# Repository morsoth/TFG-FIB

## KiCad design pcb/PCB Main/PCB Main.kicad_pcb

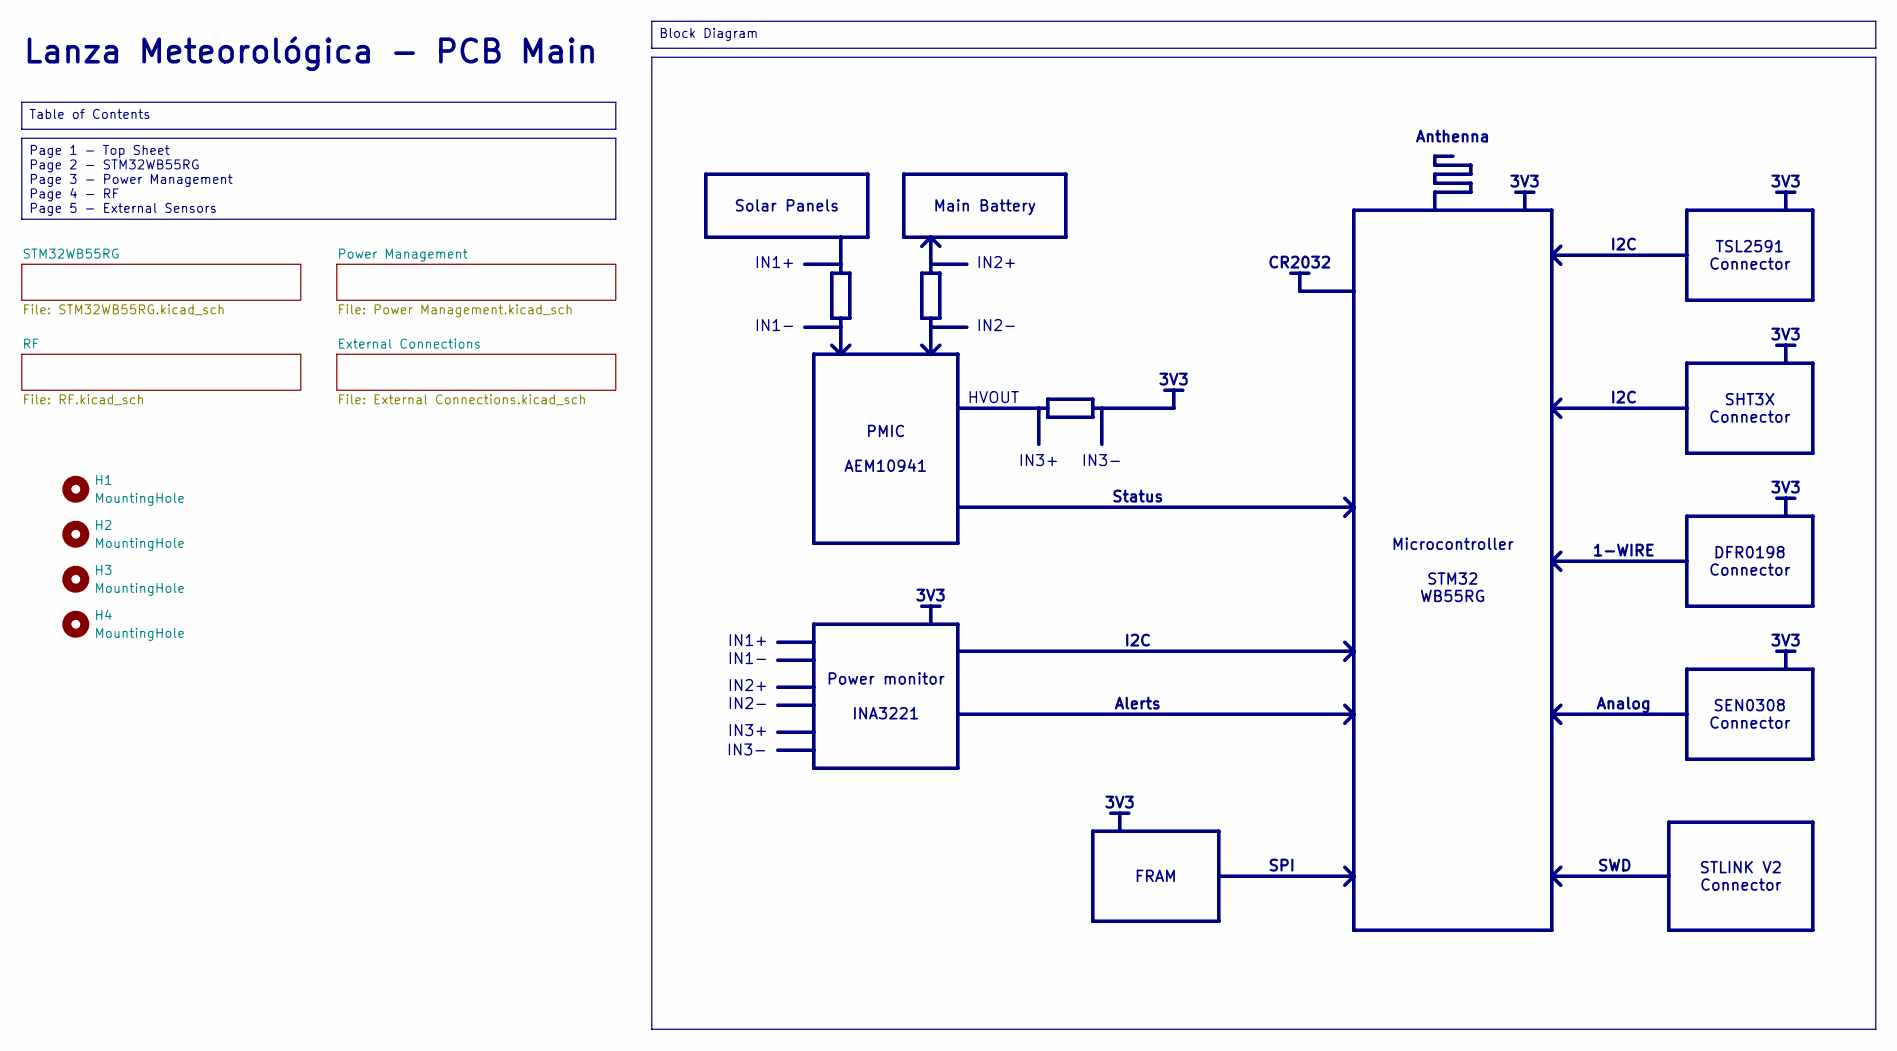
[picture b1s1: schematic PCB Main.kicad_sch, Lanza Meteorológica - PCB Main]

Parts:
H1, H2, H3, H4: MountingHole; MountingHole_2.2mm_M2

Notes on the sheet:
3V3
IN3+
IN2-
SPI
IN1-
Analog
I2C
Anthenna
IN1+
IN3-
Status
Lanza Meteorológica - PCB Main
HVOUT
SWD
IN2+
1-WIRE
Alerts
CR2032
PMIC AEM10941
Page 1 - Top Sheet Page 2 - STM32WB55RG Page 3 - Power Management Page 4 - RF Page 5 - External Sensors
SHT3X Connector
Solar Panels
STLINK V2 Connector
Table of Contents
FRAM
Main Battery
Block Diagram
DFR0198 Connector
Microcontroller STM32 WB55RG
SEN0308 Connector
TSL2591 Connector
Power monitor INA3221

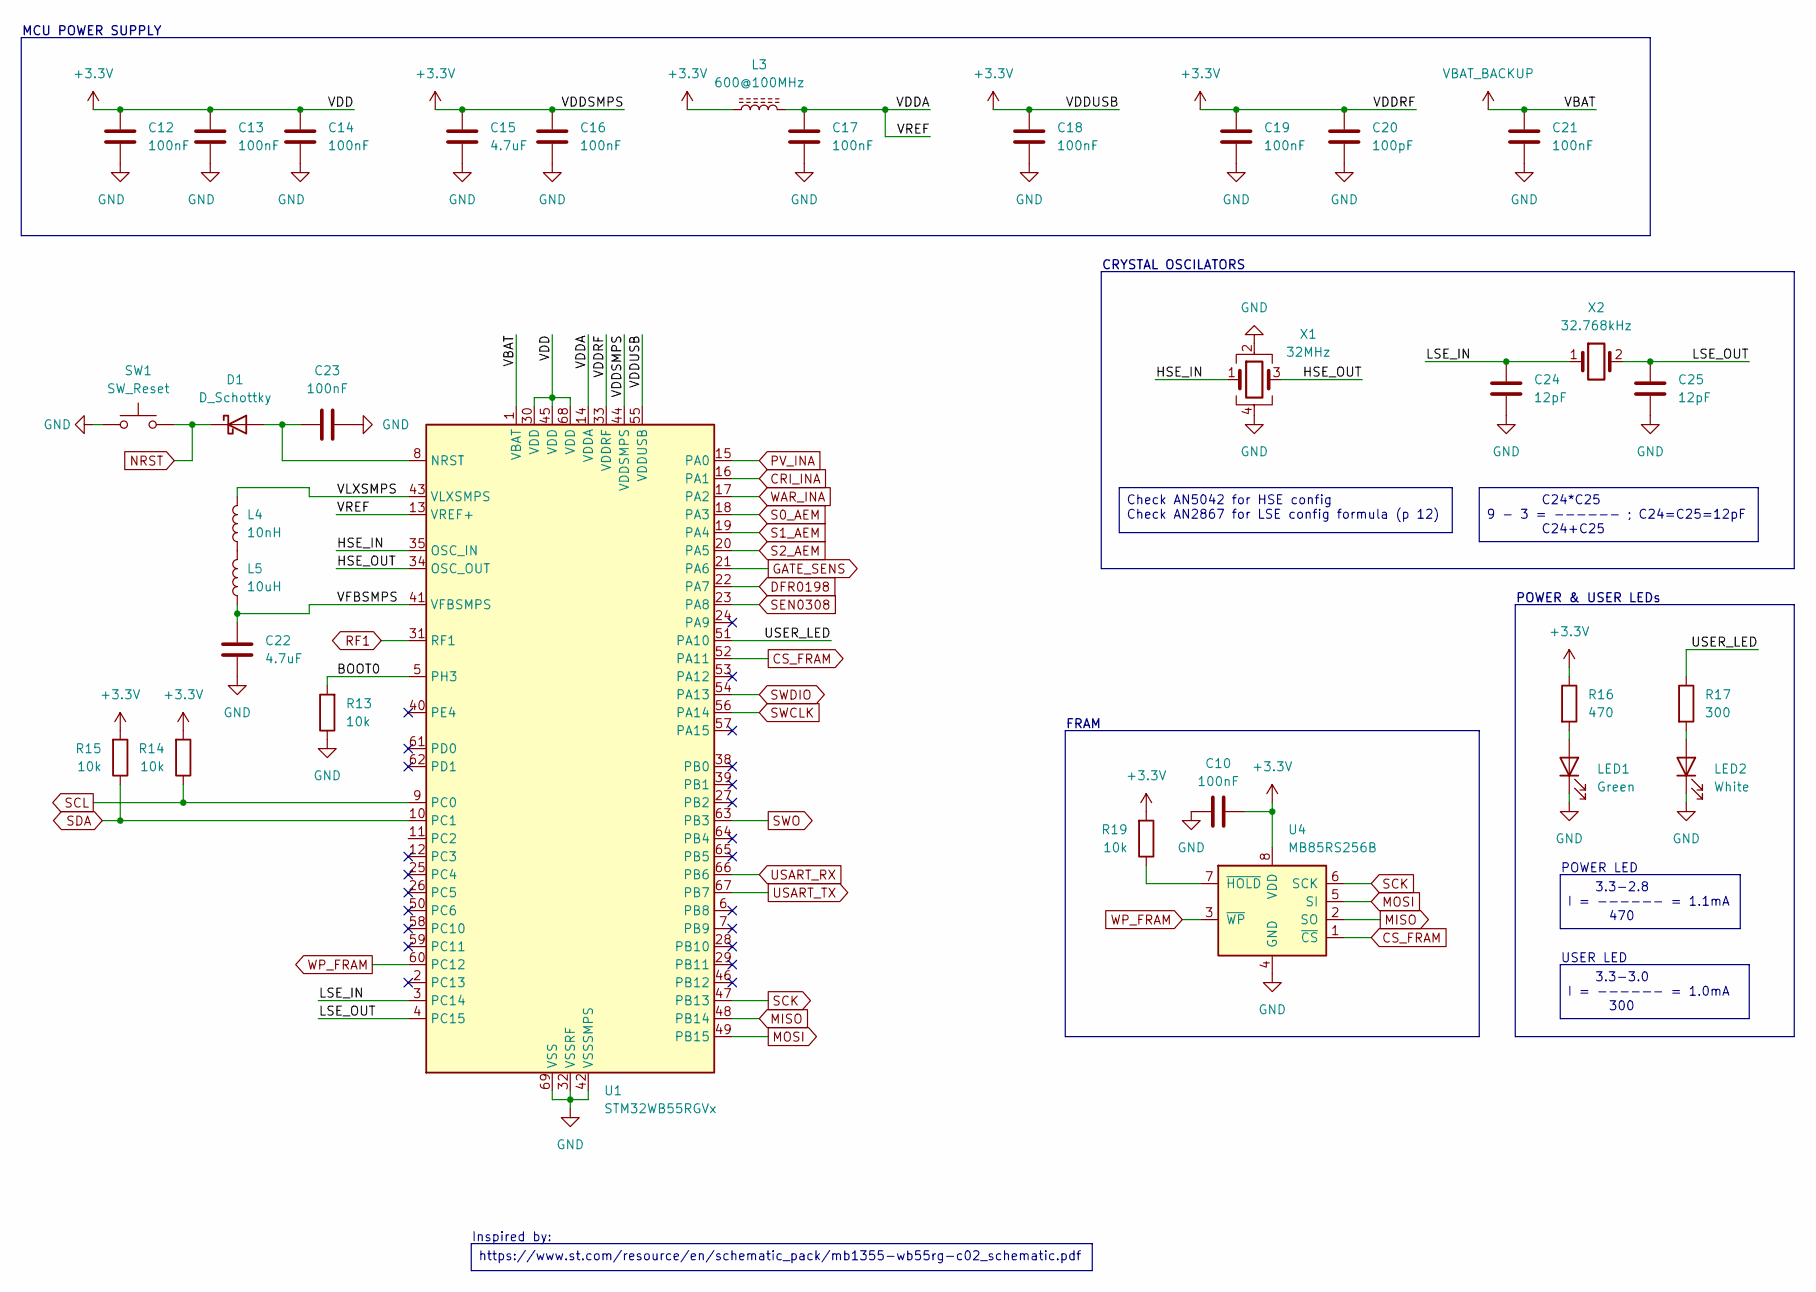
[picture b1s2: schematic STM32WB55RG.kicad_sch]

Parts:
C10, C12, C13, C14, C16, C17, C18, C19, C21, C23: 100nF; C_0402_1005Metric
C15, C22: 4.7uF; C_0402_1005Metric
C20: 100pF; C_0402_1005Metric
C24, C25: 12pF; C_0402_1005Metric
D1: D_Schottky; D_SOD-323
L3: 600@100MHz; L_0603_1608Metric
L4: 10nH; L_0402_1005Metric
L5: 10uH; L_0805_2012Metric
LED1: Green; LED_0805_2012Metric
LED2: White; LED_0805_2012Metric
R13, R14, R15, R19: 10k; R_0402_1005Metric
R16: 470; R_0603_1608Metric
R17: 300; R_0603_1608Metric
SW1: SW_Reset; SW_SPST_TL3342
U1: STM32WB55RGVx; QFN-68-1EP_8x8mm_P0.4mm_EP6.4x6.4mm
U4: MB85RS256B; SOIC-8_3.9x4.9mm_P1.27mm
X1: 32MHz; Crystal_SMD_2016-4Pin_2.0x1.6mm
X2: 32.768kHz; Crystal_SMD_2012-2Pin_2.0x1.2mm

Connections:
+3.3V: C10.1, C12.2, C13.2, C14.2, C15.2, C16.2, C18.2, C19.2, C20.2, L3.1, R14.2, R15.2, R16.1, R19.2, U1.30 (VDD), U1.33 (VDDRF), U1.44 (VDDSMPS), U1.45 (VDD), U1.55 (VDDUSB), U1.68 (VDD), U4.8 (VDD); also elsewhere on the board
/STM32WB55RG/BOOT0: R13.2, U1.5 (PH3)
/STM32WB55RG/HSE_IN: U1.35 (OSC_IN), X1.1
/STM32WB55RG/HSE_OUT: U1.34 (OSC_OUT), X1.3
/STM32WB55RG/LSE_IN: C24.2, U1.3 (PC14), X2.1
/STM32WB55RG/LSE_OUT: C25.2, U1.4 (PC15), X2.2
/STM32WB55RG/USER_LED: R17.1, U1.51 (PA10)
/STM32WB55RG/VDDA: C17.2, L3.2, U1.13 (VREF+), U1.14 (VDDA)
/STM32WB55RG/VFBSMPS: C22.2, L5.1, U1.41 (VFBSMPS)
/STM32WB55RG/VLXSMPS: L4.2, U1.43 (VLXSMPS)
CRI_INA: U1.16 (PA1); also elsewhere on the board
CS_FRAM: U1.52 (PA11), U4.1 (~CS)
DFR0198: U1.22 (PA7); also elsewhere on the board
GATE_SENS: U1.21 (PA6); also elsewhere on the board
GND: C10.2, C12.1, C13.1, C14.1, C15.1, C16.1, C17.1, C18.1, C19.1, C20.1, C21.1, C22.1, C23.1, C24.1, C25.1, LED1.1 (K), LED2.1 (K), R13.1, SW1.1, U1.32 (VSSRF), U1.42 (VSSSMPS), U1.69 (VSS), U4.4 (GND), X1.2, X1.4; also elsewhere on the board
MISO: U1.48 (PB14), U4.2 (SO)
MOSI: U1.49 (PB15), U4.5 (SI)
NRST: D1.1 (K), SW1.2; also elsewhere on the board
unnamed: C23.2, D1.2 (A), U1.8 (NRST)
unnamed: L4.1, L5.2
unnamed: LED1.2 (A), R16.2
unnamed: LED2.2 (A), R17.2
unnamed: R19.1, U4.7 (~HOLD)
PV_INA: U1.15 (PA0); also elsewhere on the board
RF1: U1.31 (RF1); also elsewhere on the board
S0_AEM: U1.18 (PA3); also elsewhere on the board
S1_AEM: U1.19 (PA4); also elsewhere on the board
S2_AEM: U1.20 (PA5); also elsewhere on the board
SCK: U1.47 (PB13), U4.6 (SCK)
SCL: R14.1, U1.9 (PC0); also elsewhere on the board
SDA: R15.1, U1.10 (PC1); also elsewhere on the board
SEN0308: U1.23 (PA8); also elsewhere on the board
SWCLK: U1.56 (PA14); also elsewhere on the board
SWDIO: U1.54 (PA13); also elsewhere on the board
SWO: U1.63 (PB3); also elsewhere on the board
USART_RX: U1.66 (PB6); also elsewhere on the board
USART_TX: U1.67 (PB7); also elsewhere on the board
VBAT_BACKUP: C21.2, U1.1 (VBAT); also elsewhere on the board
WAR_INA: U1.17 (PA2); also elsewhere on the board
WP_FRAM: U1.60 (PC12), U4.3 (~WP)

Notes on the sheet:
Inspired by:
CRYSTAL OSCILATORS
POWER & USER LEDs
FRAM
POWER LED
USER LED
MCU POWER SUPPLY
3.3-2.8 I = ------ = 1.1mA 470
https://www.st.com/resource/en/schematic_pack/mb1355-wb55rg-c02_schematic.pdf
Check AN5042 for HSE config Check AN2867 for LSE config formula (p 12)
3.3-3.0 I = ------ = 1.0mA 300
C24*C25 9 - 3 = ------ ; C24=C25=12pF C24+C25

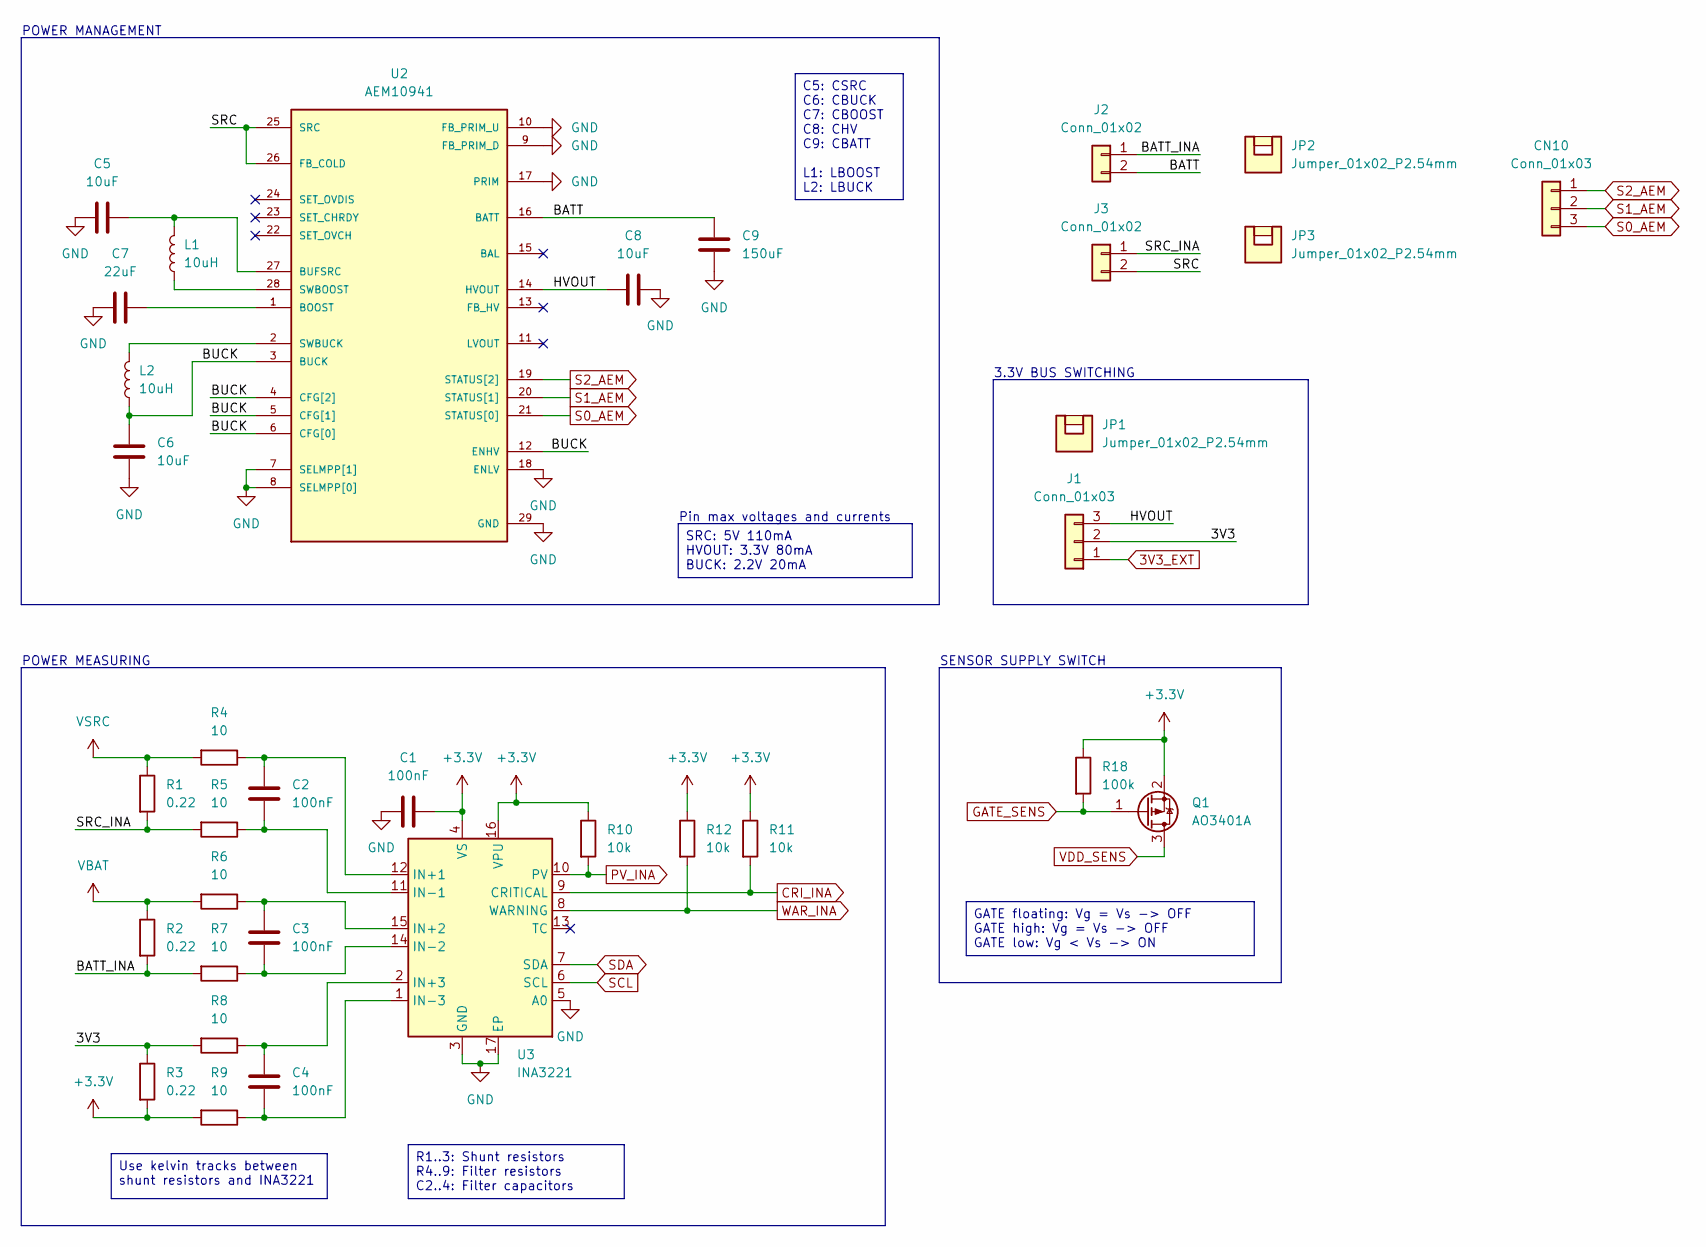
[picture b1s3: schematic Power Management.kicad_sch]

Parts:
C1, C2, C3, C4: 100nF; C_0402_1005Metric
C5, C6, C8: 10uF; C_0603_1608Metric
C7: 22uF; C_0603_1608Metric
C9: 150uF; C_1206_3216Metric
CN10: Conn_01x03; PinHeader_1x03_P2.54mm_Vertical
J1: Conn_01x03; PinHeader_1x03_P2.54mm_Vertical
J2, J3: Conn_01x02; PinHeader_1x02_P2.54mm_Vertical
JP1, JP2, JP3: Jumper_01x02_P2.54mm
L1: 10uH; L_Coilcraft_LPS4018
L2: 10uH; L_0603_1608Metric
Q1: AO3401A; SOT-23
R1, R2, R3: 0.22; R_2512_6332Metric
R4, R5, R6, R7, R8, R9: 10; R_0402_1005Metric
R10, R11, R12: 10k; R_0402_1005Metric
R18: 100k; R_0603_1608Metric
U2: AEM10941; QFN50P500X500X90-29N
U3: INA3221; Texas_RGV0016A_VQFN-16-1EP_4x4mm_P0.65mm_EP2.1x2.1mm

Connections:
3V3_EXT: J1.1; also elsewhere on the board
+3.3V: C1.2, Q1.2 (S), R3.2, R9.2, R10.1, R11.1, R12.1, R18.1, U3.4 (VS), U3.16 (VPU); also elsewhere on the board
/Power Management/3V3: J1.2, R3.1, R8.2
/Power Management/BATT: C9.1, J2.2, U2.16 (BATT)
/Power Management/BATT_INA: J2.1, R2.2, R7.2
/Power Management/BUCK: C6.1, L2.1, U2.3 (BUCK), U2.4 (CFG[2]), U2.5 (CFG[1]), U2.6 (CFG[0]), U2.12 (ENHV)
/Power Management/HVOUT: C8.2, J1.3, U2.14 (HVOUT)
/Power Management/SRC: J3.2, U2.25 (SRC), U2.26 (FB_COLD)
/Power Management/SRC_INA: J3.1, R1.2, R5.2
CRI_INA: R11.2, U3.9 (CRITICAL); also elsewhere on the board
GATE_SENS: Q1.1 (G), R18.2; also elsewhere on the board
GND: C1.1, C5.2, C6.2, C7.2, C8.1, C9.2, U2.7 (SELMPP[1]), U2.8 (SELMPP[0]), U2.9 (FB_PRIM_D), U2.10 (FB_PRIM_U), U2.17 (PRIM), U2.18 (ENLV), U2.29 (GND), U3.3 (GND), U3.5 (A0), U3.17 (EP); also elsewhere on the board
unnamed: C7.1, U2.1 (BOOST)
unnamed: C5.1, L1.2, U2.27 (BUFSRC)
unnamed: L1.1, U2.28 (SWBOOST)
unnamed: L2.2, U2.2 (SWBUCK)
unnamed: C2.2, R4.1, U3.12 (IN+1)
unnamed: C3.2, R6.1, U3.15 (IN+2)
unnamed: C4.2, R8.1, U3.2 (IN+3)
unnamed: C2.1, R5.1, U3.11 (IN-1)
unnamed: C3.1, R7.1, U3.14 (IN-2)
unnamed: C4.1, R9.1, U3.1 (IN-3)
PV_INA: R10.2, U3.10 (PV); also elsewhere on the board
S0_AEM: CN10.3, U2.21 (STATUS[0]); also elsewhere on the board
S1_AEM: CN10.2, U2.20 (STATUS[1]); also elsewhere on the board
S2_AEM: CN10.1, U2.19 (STATUS[2]); also elsewhere on the board
SCL: U3.6 (SCL); also elsewhere on the board
SDA: U3.7 (SDA); also elsewhere on the board
VBAT: R2.1, R6.2; also elsewhere on the board
VDD_SENS: Q1.3 (D); also elsewhere on the board
VSRC: R1.1, R4.2; also elsewhere on the board
WAR_INA: R12.2, U3.8 (WARNING); also elsewhere on the board

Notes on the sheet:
SENSOR SUPPLY SWITCH
3.3V BUS SWITCHING
POWER MANAGEMENT
Pin max voltages and currents
POWER MEASURING
SRC: 5V 110mA HVOUT: 3.3V 80mA BUCK: 2.2V 20mA
Use kelvin tracks between shunt resistors and INA3221
C5: CSRC C6: CBUCK C7: CBOOST C8: CHV C9: CBATT L1: LBOOST L2: LBUCK
R1..3: Shunt resistors R4..9: Filter resistors C2..4: Filter capacitors
GATE floating: Vg = Vs -> OFF GATE high: Vg = Vs -> OFF GATE low: Vg < Vs -> ON

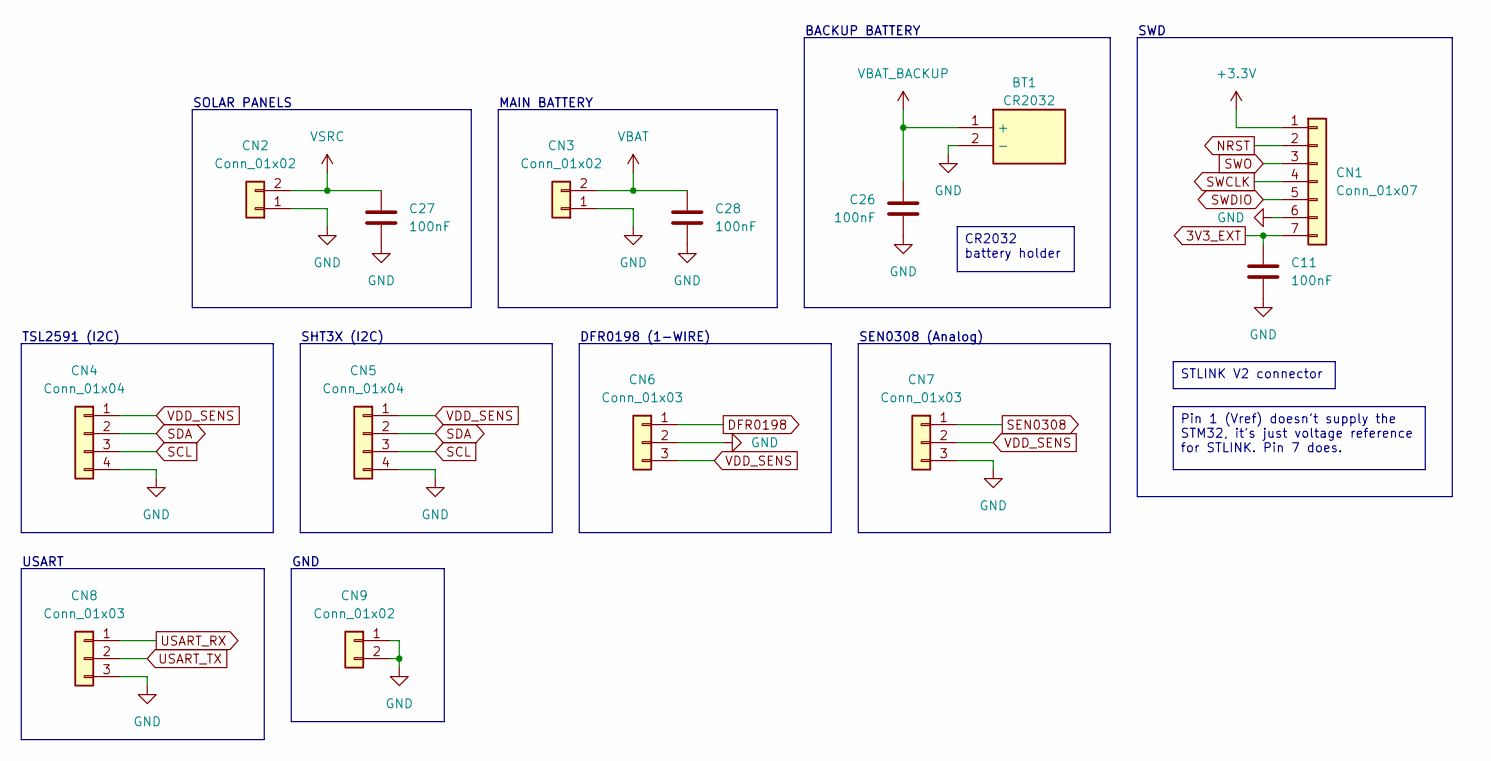
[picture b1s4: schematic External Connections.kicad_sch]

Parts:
BT1: CR2032; 1066
C11, C26, C27, C28: 100nF; C_0402_1005Metric
CN1: Conn_01x07; PinHeader_1x07_P2.54mm_Vertical
CN2, CN3: Conn_01x02; JST_EH_S2B-EH_1x02_P2.50mm_Horizontal
CN4, CN5: Conn_01x04; PinHeader_1x04_P2.54mm_Horizontal
CN6, CN7: Conn_01x03; PinHeader_1x03_P2.54mm_Horizontal
CN8: Conn_01x03; PinHeader_1x03_P2.54mm_Vertical
CN9: Conn_01x02; PinHeader_1x02_P2.54mm_Vertical

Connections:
3V3_EXT: C11.2, CN1.7; also elsewhere on the board
+3.3V: CN1.1; also elsewhere on the board
DFR0198: CN6.1; also elsewhere on the board
GND: BT1.2 (-), C11.1, C26.1, C27.1, C28.1, CN1.6, CN2.1, CN3.1, CN4.4, CN5.4, CN6.2, CN7.3, CN8.3, CN9.1, CN9.2; also elsewhere on the board
NRST: CN1.2; also elsewhere on the board
SCL: CN4.3, CN5.3; also elsewhere on the board
SDA: CN4.2, CN5.2; also elsewhere on the board
SEN0308: CN7.1; also elsewhere on the board
SWCLK: CN1.4; also elsewhere on the board
SWDIO: CN1.5; also elsewhere on the board
SWO: CN1.3; also elsewhere on the board
USART_RX: CN8.1; also elsewhere on the board
USART_TX: CN8.2; also elsewhere on the board
VBAT: C28.2, CN3.2; also elsewhere on the board
VBAT_BACKUP: BT1.1 (+), C26.2; also elsewhere on the board
VDD_SENS: CN4.1, CN5.1, CN6.3, CN7.2; also elsewhere on the board
VSRC: C27.2, CN2.2; also elsewhere on the board

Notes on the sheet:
MAIN BATTERY
SEN0308 (Analog)
SHT3X (I2C)
BACKUP BATTERY
DFR0198 (1-WIRE)
GND
SOLAR PANELS
SWD
TSL2591 (I2C)
USART
STLINK V2 connector
Pin 1 (Vref) doesn't supply the STM32, it's just voltage reference for STLINK. Pin 7 does.
CR2032 battery holder

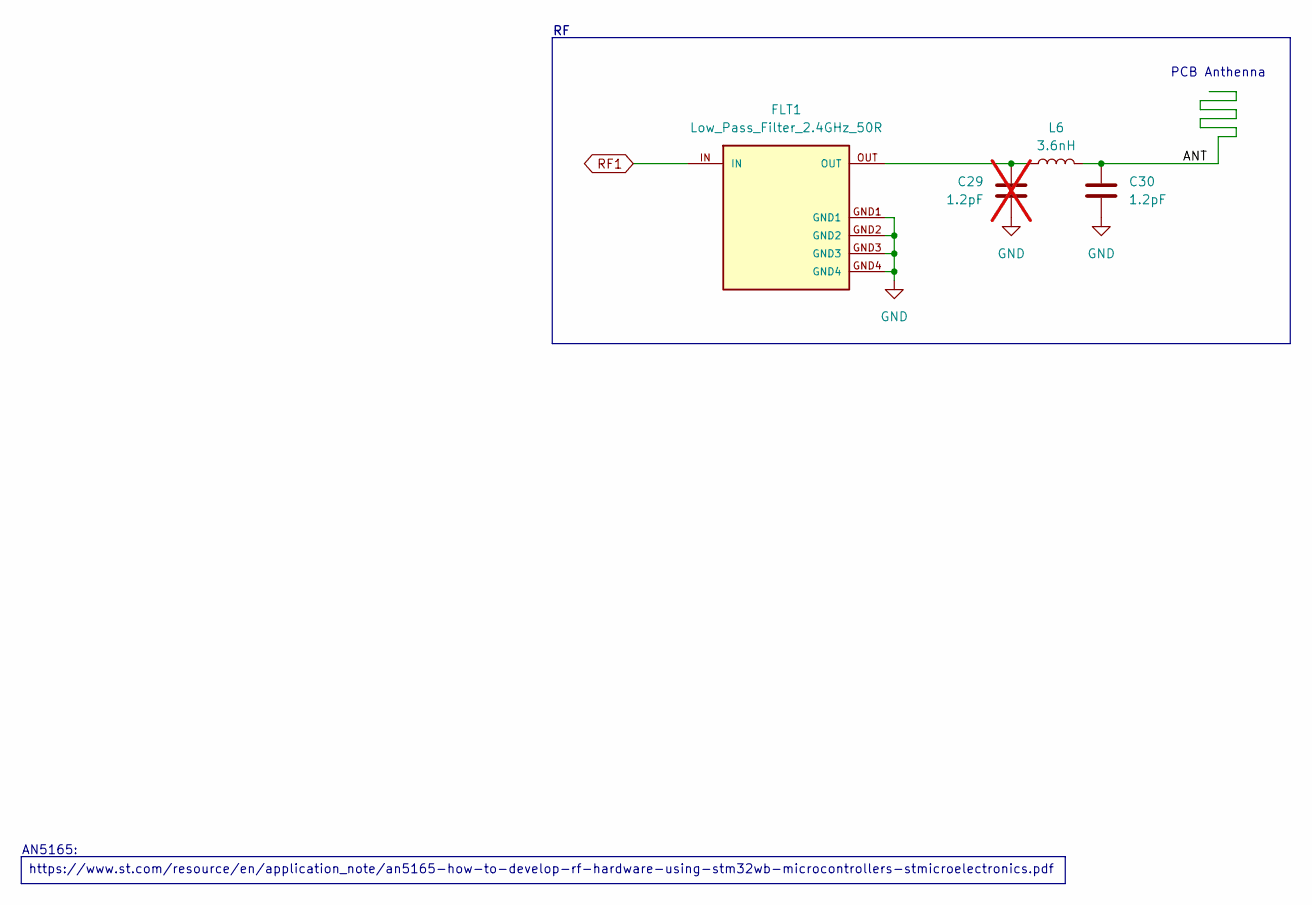
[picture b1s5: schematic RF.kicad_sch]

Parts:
C29: 1.2pF; C_0402_1005Metric; not fitted
C30: 1.2pF; C_0402_1005Metric
FLT1: Low_Pass_Filter_2.4GHz_50R; MLPF-WB55-01E3
L6: 3.6nH; LED_0402_1005Metric

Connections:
/RF/ANT: C30.2, L6.2
GND: C29.1, C30.1, FLT1.GND1, FLT1.GND2, FLT1.GND3, FLT1.GND4; also elsewhere on the board
unnamed: C29.2, FLT1.OUT, L6.1
RF1: FLT1.IN; also elsewhere on the board

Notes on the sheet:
PCB Anthenna
AN5165:
https://www.st.com/resource/en/application_note/an5165-how-to-develop-rf-hardware-using-stm32wb-microcontrollers-stmicroelectronics.pdf

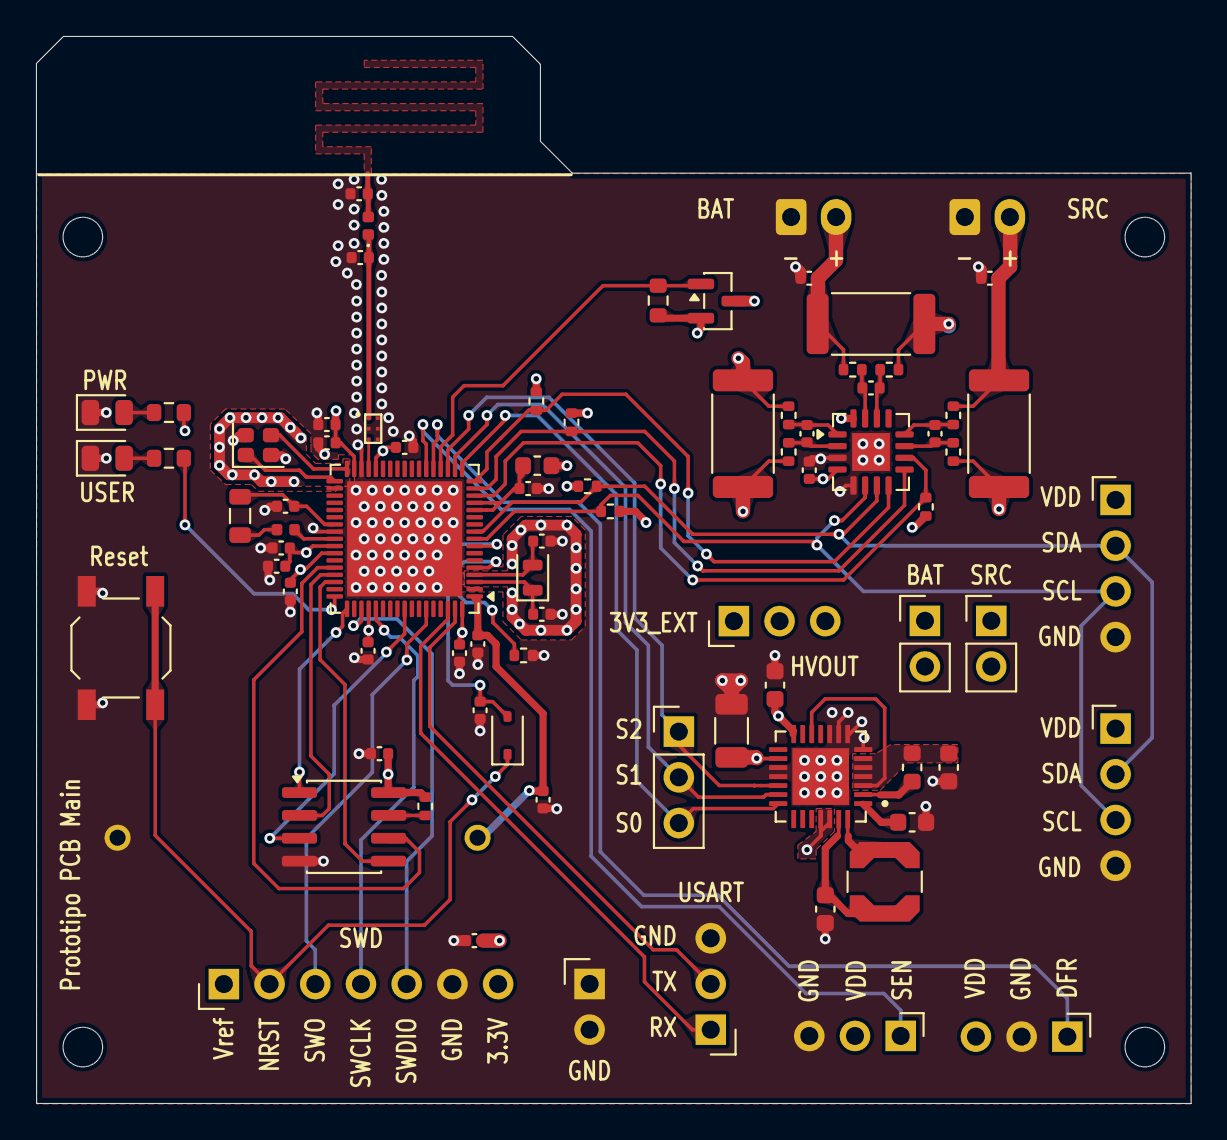
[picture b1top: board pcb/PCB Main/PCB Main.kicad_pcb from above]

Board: 4 copper layers, 64.1 x 59.3 mm, 85 parts (1 on the bottom side), 63 nets.

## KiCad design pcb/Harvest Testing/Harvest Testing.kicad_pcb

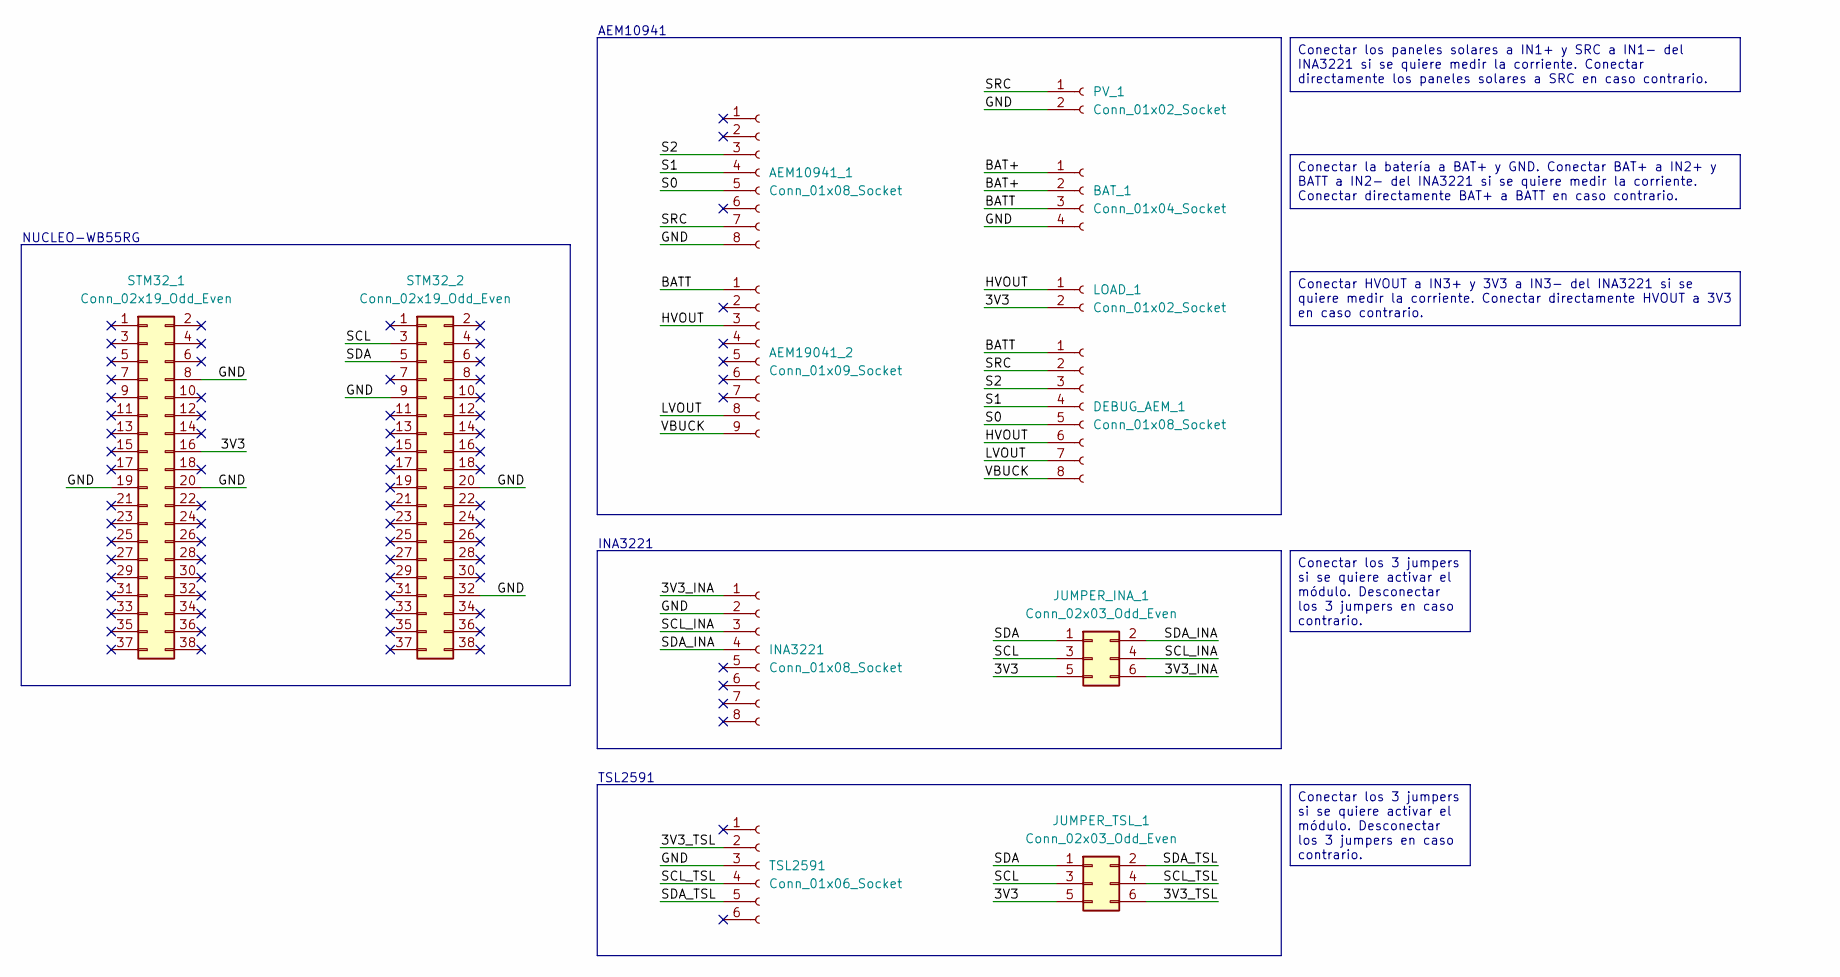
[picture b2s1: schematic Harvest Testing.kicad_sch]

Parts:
AEM10941_1: Conn_01x08_Socket; PinSocket_1x08_P2.54mm_Vertical
AEM19041_2: Conn_01x09_Socket; PinSocket_1x09_P2.54mm_Vertical
BAT_1: Conn_01x04_Socket; PinSocket_1x04_P2.54mm_Vertical
DEBUG_AEM_1: Conn_01x08_Socket; PinHeader_1x08_P2.54mm_Vertical
INA3221: Conn_01x08_Socket; PinSocket_1x08_P2.54mm_Vertical
JUMPER_INA_1: Conn_02x03_Odd_Even; PinHeader_2x03_P2.54mm_Vertical
JUMPER_TSL_1: Conn_02x03_Odd_Even; PinHeader_2x03_P2.54mm_Vertical
LOAD_1: Conn_01x02_Socket; PinSocket_1x02_P2.54mm_Vertical
PV_1: Conn_01x02_Socket; PinSocket_1x02_P2.54mm_Vertical
STM32_1, STM32_2: Conn_02x19_Odd_Even; PinSocket_2x19_P2.54mm_Vertical
TSL2591: Conn_01x06_Socket; PinSocket_1x06_P2.54mm_Vertical

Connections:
/3V3: JUMPER_INA_1.5, JUMPER_TSL_1.5, LOAD_1.2, STM32_1.16
/3V3_INA: INA3221.1, JUMPER_INA_1.6
/3V3_TSL: JUMPER_TSL_1.6, TSL2591.2
/BAT+: BAT_1.1, BAT_1.2
/BATT: AEM19041_2.1, BAT_1.3, DEBUG_AEM_1.1
/GND: AEM10941_1.8, BAT_1.4, INA3221.2, PV_1.2, STM32_1.8, STM32_1.19, STM32_1.20, STM32_2.9, STM32_2.20, STM32_2.32, TSL2591.3
/HVOUT: AEM19041_2.3, DEBUG_AEM_1.6, LOAD_1.1
/LVOUT: AEM19041_2.8, DEBUG_AEM_1.7
/S0: AEM10941_1.5, DEBUG_AEM_1.5
/S1: AEM10941_1.4, DEBUG_AEM_1.4
/S2: AEM10941_1.3, DEBUG_AEM_1.3
/SCL: JUMPER_INA_1.3, JUMPER_TSL_1.3, STM32_2.3
/SCL_INA: INA3221.3, JUMPER_INA_1.4
/SCL_TSL: JUMPER_TSL_1.4, TSL2591.4
/SDA: JUMPER_INA_1.1, JUMPER_TSL_1.1, STM32_2.5
/SDA_INA: INA3221.4, JUMPER_INA_1.2
/SDA_TSL: JUMPER_TSL_1.2, TSL2591.5
/SRC: AEM10941_1.7, DEBUG_AEM_1.2, PV_1.1
/VBUCK: AEM19041_2.9, DEBUG_AEM_1.8

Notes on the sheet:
TSL2591
AEM10941
NUCLEO-WB55RG
INA3221
Conectar la batería a BAT+ y GND. Conectar BAT+ a IN2+ y BATT a IN2- del INA3221 si se quiere medir la corriente. Conectar directamente BAT+ a BATT en caso contrario.
Conectar HVOUT a IN3+ y 3V3 a IN3- del INA3221 si se quiere medir la corriente. Conectar directamente HVOUT a 3V3 en caso contrario.
Conectar los 3 jumpers si se quiere activar el módulo. Desconectar los 3 jumpers en caso contrario.
Conectar los paneles solares a IN1+ y SRC a IN1- del INA3221 si se quiere medir la corriente. Conectar directamente los paneles solares a SRC en caso contrario.

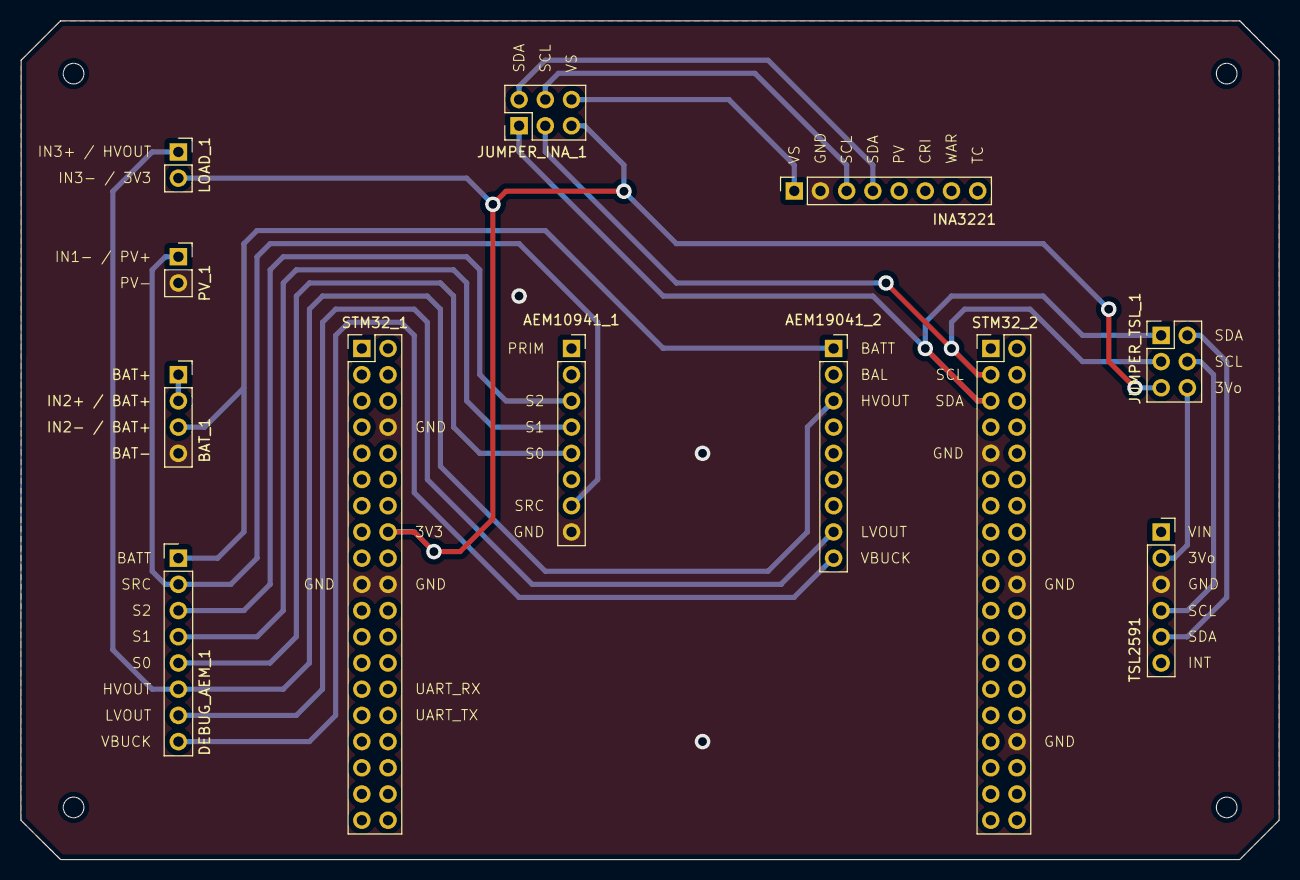
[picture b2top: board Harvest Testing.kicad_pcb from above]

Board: 2 copper layers, 121.9 x 81.3 mm, 12 parts (0 on the bottom side), 19 nets.

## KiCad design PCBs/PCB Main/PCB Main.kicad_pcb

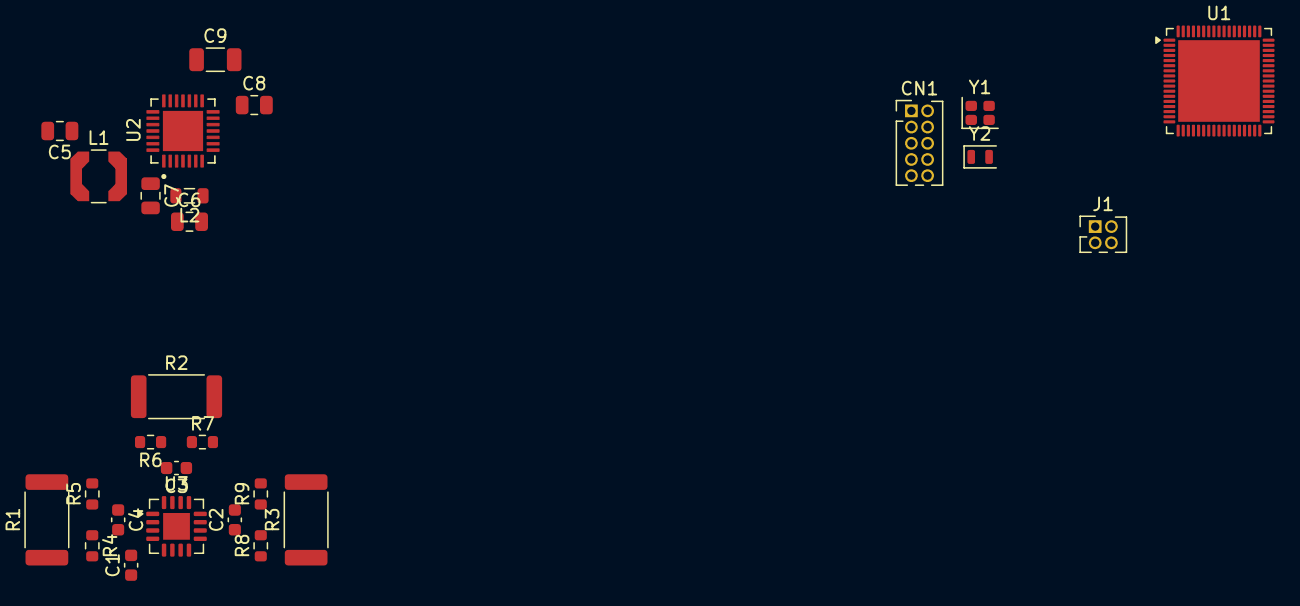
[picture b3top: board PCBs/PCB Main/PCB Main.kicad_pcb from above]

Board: 2 copper layers, 27 parts (0 on the bottom side), 31 nets, no tracks yet.

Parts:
C1: 0.1uF; C_0603_1608Metric
C2, C3, C4: 33nF; C_0603_1608Metric
C5, C6, C8: 10uF; C_0805_2012Metric
C7: 22uF; C_0805_2012Metric
C9: 150uF; C_1206_3216Metric
CN1: Conn_ARM_JTAG_SWD_10; PinHeader_2x05_P1.27mm_Vertical
J1: Conn_02x02_Odd_Even; PinHeader_2x02_P1.27mm_Vertical
L1: 10uH; L_Coilcraft_LPS4018
L2: 10uH; L_0805_2012Metric
R1, R2, R3: 0.1; R_2512_6332Metric
R4, R5, R6, R7, R8, R9: 10; R_0603_1608Metric
U1: STM32WB55RGVx; QFN-68-1EP_8x8mm_P0.4mm_EP6.4x6.4mm
U2: AEM10941; QFN50P500X500X90-29N
U3: INA3221; Texas_RGV0016A_VQFN-16-1EP_4x4mm_P0.65mm_EP2.1x2.1mm
Y1: HSE; Crystal_SMD_2016-4Pin_2.0x1.6mm
Y2: LSE; Crystal_SMD_2012-2Pin_2.0x1.2mm

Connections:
/Power Management/BAT+: R2.1, R6.2
/Power Management/BAT-: R2.2, R7.2
/Power Management/BATT: C9.1, U2.16 (BATT)
/Power Management/BUCK: C6.2, L2.1, U2.3 (BUCK), U2.4 (CFG[2]), U2.5 (CFG[1]), U2.6 (CFG[0]), U2.12 (ENHV)
/Power Management/HVOUT: C8.1, J1.1, U2.14 (HVOUT)
/Power Management/LOAD+: R3.1, R8.2
/Power Management/LOAD-: R3.2, R9.2
/Power Management/PV+: R1.1, R4.2
/Power Management/PV-: R1.2, R5.2
/STM32WB55RG/NRST: CN1.10 (~RESET), U1.8 (NRST)
/STM32WB55RG/OSC32_IN: U1.3 (PC14), Y2.1
/STM32WB55RG/OSC32_OUT: U1.4 (PC15), Y2.2
/STM32WB55RG/OSC_IN: U1.35 (OSC_IN), Y1.1
/STM32WB55RG/OSC_OUT: U1.34 (OSC_OUT), Y1.3
/STM32WB55RG/SWCLK: CN1.4 (SWCLK/TCK), U1.56 (PA14)
/STM32WB55RG/SWDIO: CN1.2 (SWDIO/TMS), U1.54 (PA13)
/STM32WB55RG/SWO: CN1.6 (SWO/TDO), U1.63 (PB3)
GND: C1.1, C5.2, C6.1, C7.2, C8.2, C9.2, CN1.3 (GND), CN1.5 (GND), CN1.9 (GNDDetect), U1.32 (VSSRF), U1.42 (VSSSMPS), U1.69 (VSS), U2.7 (SELMPP[1]), U2.8 (SELMPP[0]), U2.9 (FB_PRIM_D), U2.10 (FB_PRIM_U), U2.17 (PRIM), U2.18 (ENLV), U2.29 (GND), U3.3 (GND), U3.5 (A0), U3.17 (EP), Y1.2, Y1.4
unnamed: C7.1, U2.1 (BOOST)
unnamed: C5.1, L1.1, U2.27 (BUFSRC)
unnamed: L1.2, U2.28 (SWBOOST)
unnamed: L2.2, U2.2 (SWBUCK)
unnamed: C2.2, R4.1, U3.12 (IN+1)
unnamed: C3.2, R6.1, U3.15 (IN+2)
unnamed: C4.2, R8.1, U3.2 (IN+3)
unnamed: C2.1, R5.1, U3.11 (IN-1)
unnamed: C3.1, R7.1, U3.14 (IN-2)
unnamed: C4.1, R9.1, U3.1 (IN-3)
SCL: U1.6 (PB8), U3.6 (SCL)
SDA: U1.7 (PB9), U3.7 (SDA)
VDD: C1.2, CN1.1 (VTref), J1.2, J1.4, U1.30 (VDD), U1.33 (VDDRF), U1.44 (VDDSMPS), U1.45 (VDD), U1.55 (VDDUSB), U1.68 (VDD), U3.4 (VS)

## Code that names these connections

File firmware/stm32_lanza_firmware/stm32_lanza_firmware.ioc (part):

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Mcu.Name=STM32WB55RGVx
Mcu.Package=VFQFPN68
Mcu.UserName=STM32WB55RGVx
PA0.GPIOParameters=GPIO_Label
PA0.GPIO_Label=PV_INA
PA0.Signal=GPXTI0
PA1.GPIOParameters=GPIO_Label
PA1.GPIO_Label=CRI_INA
PA1.Signal=GPXTI1
PA10.GPIOParameters=GPIO_Label
PA10.GPIO_Label=USER_LED
PA10.Signal=GPIO_Output
PA11.GPIOParameters=GPIO_Label
PA11.GPIO_Label=CS_FRAM
PA11.Signal=GPIO_Output
PA13.Mode=Serial_Wire
PA13.Signal=SYS_JTMS-SWDIO
PA14.Mode=Serial_Wire
PA14.Signal=SYS_JTCK-SWCLK
PA2.GPIOParameters=GPIO_Label
PA2.GPIO_Label=WAR_INA
PA2.Signal=GPXTI2
PA3.GPIOParameters=GPIO_Label,GPIO_ModeDefaultEXTI
PA3.GPIO_Label=S0_AEM
PA3.GPIO_ModeDefaultEXTI=GPIO_MODE_IT_RISING_FALLING
PA3.Signal=GPXTI3
PA4.GPIOParameters=GPIO_Label
PA4.GPIO_Label=S1_AEM
PA4.Signal=GPXTI4
PA5.GPIOParameters=GPIO_Label
PA5.GPIO_Label=S2_AEM
PA5.Signal=GPIO_Input
PA6.GPIOParameters=GPIO_Label
PA6.GPIO_Label=GATE_SENS
PA6.Signal=GPIO_Output
PA7.GPIOParameters=PinState,GPIO_PuPd,GPIO_Label,GPIO_ModeDefaultOutputPP
PA7.GPIO_Label=DFR0198
PA7.GPIO_ModeDefaultOutputPP=GPIO_MODE_OUTPUT_OD
PA7.GPIO_PuPd=GPIO_PULLUP
PA7.PinState=GPIO_PIN_SET
PA7.Signal=GPIO_Output
PA8.GPIOParameters=GPIO_Label
PA8.GPIO_Label=SEN0308
PA8.Signal=ADCx_IN15
PB13.Mode=Full_Duplex_Master
PB13.Signal=SPI2_SCK
PB14.Mode=Full_Duplex_Master
PB14.Signal=SPI2_MISO
PB15.Mode=Full_Duplex_Master
PB15.Signal=SPI2_MOSI
PB6.GPIOParameters=GPIO_Label
PB6.GPIO_Label=USART_RX
PB6.Mode=Asynchronous
PB6.Signal=USART1_TX
PB7.GPIOParameters=GPIO_Label
PB7.GPIO_Label=USART_TX
PB7.Mode=Asynchronous
PB7.Signal=USART1_RX
PC0.GPIOParameters=GPIO_Pu
PC0.GPIO_Pu=GPIO_PULLUP
PC0.Mode=I2C
PC0.Signal=I2C3_SCL
PC1.GPIOParameters=GPIO_Pu
PC1.GPIO_Pu=GPIO_PULLUP
PC1.Mode=I2C
PC1.Signal=I2C3_SDA
PC12.GPIOParameters=GPIO_Label
PC12.GPIO_Label=WP_FRAM
PC12.Signal=GPIO_Output
PC14-OSC32_IN.Mode=LSE-External-Oscillator
PC14-OSC32_IN.Signal=RCC_OSC32_IN
PC15-OSC32_OUT.Mode=LSE-External-Oscillator
PC15-OSC32_OUT.Signal=RCC_OSC32_OUT
RCC.HSE_VALUE=32000000
RCC.SYSCLKFreq_VALUE=32000000
board=NUCLEO-WB55RG
boardIOC=true

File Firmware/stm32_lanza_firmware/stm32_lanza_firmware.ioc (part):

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Mcu.Name=STM32WB55RGVx
Mcu.Package=VFQFPN68
Mcu.UserName=STM32WB55RGVx
PA0.Signal=ADCx_IN5
PA1.GPIOParameters=GPIO_PuPd,GPIO_ModeDefaultOutputPP
PA1.GPIO_ModeDefaultOutputPP=GPIO_MODE_OUTPUT_OD
PA1.GPIO_PuPd=GPIO_NOPULL
PA1.Signal=GPIO_Output
PA3.Signal=GPIO_Input
PA4.Signal=GPIO_Input
PA5.Signal=GPIO_Input
PB0.GPIOParameters=GPIO_Label
PB0.GPIO_Label=LD2 [Green Led]
PB0.Signal=GPIO_Output
PB1.GPIOParameters=GPIO_Label
PB1.GPIO_Label=LD3 [Red Led]
PB1.Signal=GPIO_Output
PB5.GPIOParameters=GPIO_Label
PB5.GPIO_Label=LD1 [Blue Led]
PB5.Signal=GPIO_Output
PB6.GPIOParameters=GPIO_Label
PB6.GPIO_Label=STLINK_RX
PB6.Mode=Asynchronous
PB6.Signal=USART1_TX
PB7.GPIOParameters=GPIO_Label
PB7.GPIO_Label=STLINK_TX
PB7.Mode=Asynchronous
PB7.Signal=USART1_RX
PB8.GPIOParameters=GPIO_Pu
PB8.GPIO_Pu=GPIO_PULLUP
PB8.Mode=I2C
PB8.Signal=I2C1_SCL
PB9.GPIOParameters=GPIO_Pu
PB9.GPIO_Pu=GPIO_PULLUP
PB9.Mode=I2C
PB9.Signal=I2C1_SDA
PC0.Mode=Asynchronous
PC0.Signal=LPUART1_RX
PC1.Mode=Asynchronous
PC1.Signal=LPUART1_TX
PC14-OSC32_IN.Mode=LSE-External-Oscillator
PC14-OSC32_IN.Signal=RCC_OSC32_IN
PC15-OSC32_OUT.Mode=LSE-External-Oscillator
PC15-OSC32_OUT.Signal=RCC_OSC32_OUT
PC4.GPIOParameters=GPIO_Label
PC4.GPIO_Label=B1 [Push Button]
PC4.Signal=GPIO_Input
PD0.GPIOParameters=GPIO_Label
PD0.GPIO_Label=B2 [Push Button]
PD0.Signal=GPIO_Input
PD1.GPIOParameters=GPIO_Label
PD1.GPIO_Label=B3 [Push Button]
PD1.Signal=GPIO_Input
RCC.HSE_VALUE=32000000
RCC.SYSCLKFreq_VALUE=32000000
board=NUCLEO-WB55RG
boardIOC=true
